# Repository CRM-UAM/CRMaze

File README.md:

# CRMaze
Open source robot for maze solving + line following

Authors
--
**Víctor Uceda & Carlos García**  
Club de Robótica-Mecatrónica, Universidad Autónoma de Madrid (CRM-UAM)  
<http://crm-uam.github.io>  

License
--
License: **Attribution - Share Alike - Creative Commons (<http://creativecommons.org/licenses/by-sa/4.0/>)**  

Disclaimer  
--
This hardware/software is provided "as is", and you use the hardware/software at your own risk. Under no circumstances shall any author be liable for direct, indirect, special, incidental, or consequential damages resulting from the use, misuse, or inability to use this hardware/software, even if the authors have been advised of the possibility of such damages.

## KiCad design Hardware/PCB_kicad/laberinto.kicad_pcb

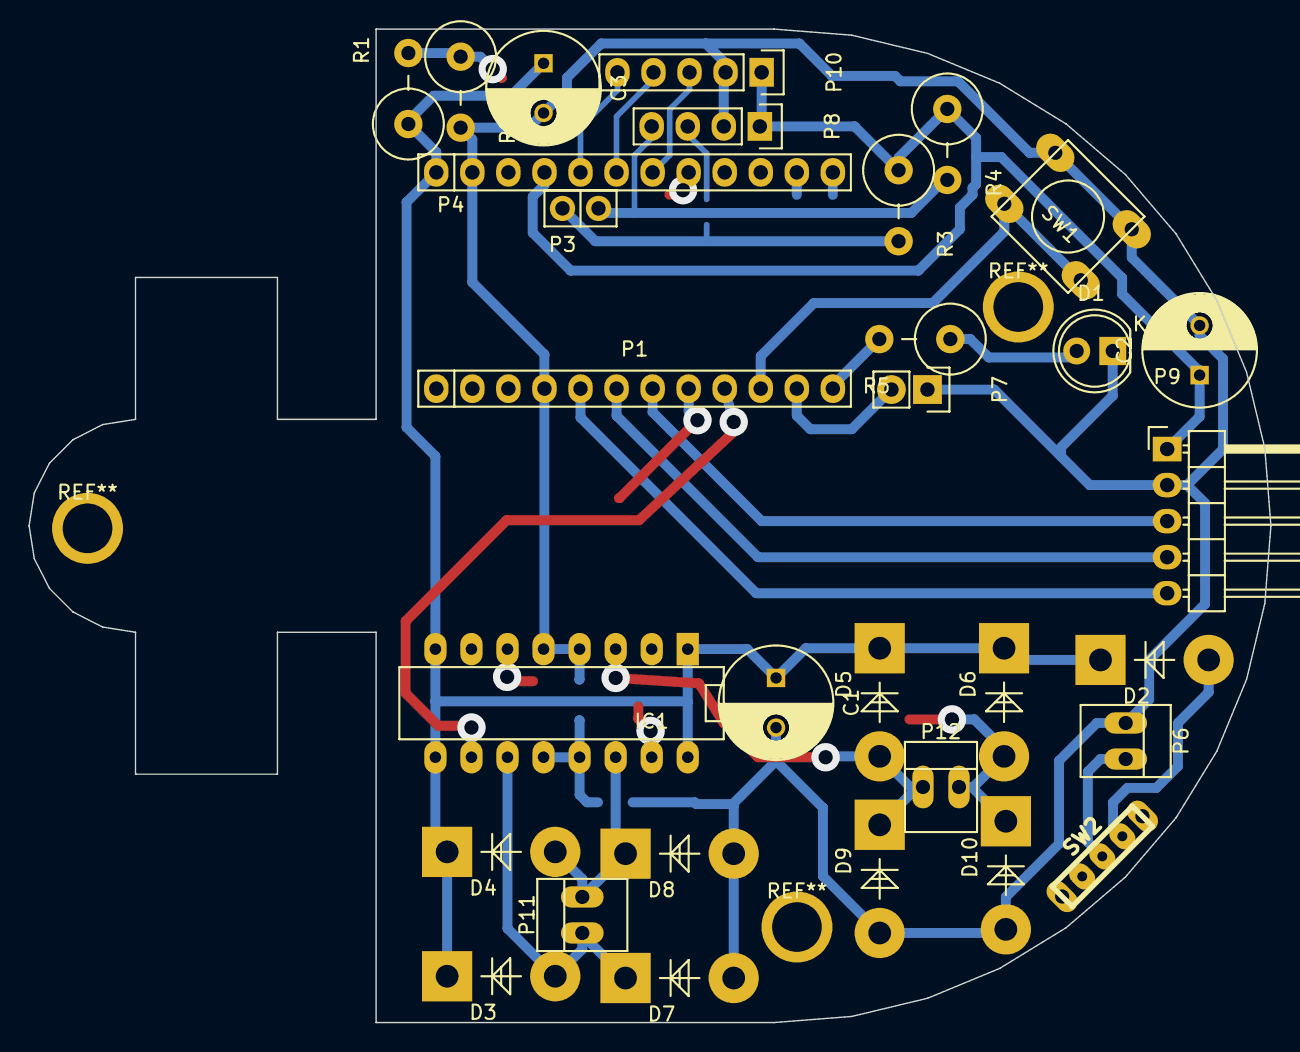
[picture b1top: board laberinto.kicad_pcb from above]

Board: 2 copper layers, 87.5 x 70.0 mm, 31 parts (0 on the bottom side), 27 nets.

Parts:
C1, C2, C3: CP; C_Radial_D8_L11.5_P3.5
D1: CLED; LED-5MM
D2: Dbatt; custom_diode
D3, D4, D5, D6, D7, D8, D9, D10: D; custom_diode
IC1: L293D; DIP-16__300_ELL
P1: Digital; Socket_Strip_Arduino_1x12
P3: ADC; Socket_Strip_Arduino_1x02
P4: Analog; Socket_Strip_Arduino_1x12
P6: batt; PINHEAD1-2
P7: buzzer; Pin_Header_Straight_1x02
P8: I2C_IMU; Pin_Header_Straight_1x04
P9: line_ir; Pin_Header_Angled_1x05
P10: distance; Pin_Header_Straight_1x05
P11: M1; PINHEAD1-2
P12: M2; PINHEAD1-2
R1, R2, R3, R4, R5: R; Resistor_Vertical_RM5mm
SW1: SW_PUSH; SW_PUSH_SMALL
SW2: SWITCH_INV; SWITCH_3Pin

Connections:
+BATT: C1.1, C3.1, D2.2, D3.2, D4.2, D5.2, D6.2, IC1.1, IC1.8, IC1.9, IC1.16, P4.1, R1.1
/Reset: P1.3, P4.3
GND: C1.2, C2.2, C3.2, D1.1, D7.1, D8.1, D9.1, D10.1, IC1.4, IC1.5, IC1.12, IC1.13, P1.4, P4.2, P6.1, P7.1, P8.2, P9.2, P10.2, R2.2, SW1.2
IR1: P4.7, P10.3
IR2: P4.6, P10.4
IR3: P4.5, P10.5
IRL: P1.7, P9.3
IRM: P1.6, P9.4
IRR: P1.5, P9.5
M1A: IC1.2, P4.11
M1Y: D5.1, D9.2, IC1.3, P12.1
M2A: IC1.7, P4.12
M2Y: D6.1, D10.2, IC1.6, P12.2
M3A: IC1.10, P1.9
M3Y: D3.1, D7.2, IC1.11, P11.1
M4A: IC1.15, P1.8
M4Y: D4.1, D8.2, IC1.14, P11.2
unnamed: D1.2, R5.1
unnamed: D2.1, SW2.1
unnamed: P6.2, SW2.2
SCL: P3.1, P8.3, R3.2
SDA: P3.2, P8.4, R4.2
VCC: C2.1, P4.4, P8.1, P9.1, P10.1, R3.1, R4.1
button: P1.10, SW1.1
buzzer: P1.11, P7.2
led: P1.12, R5.2
mbatt: P4.8, R1.2, R2.1

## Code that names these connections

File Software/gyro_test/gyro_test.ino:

// Code for the CRMaze robot
// By Víctor Uceda & Carlos García
//   Club de Robótica-Mecatrónica,
//   Universidad Autónoma de Madrid
//   http://crm-uam.github.io
// License: CC-BY-SA (http://creativecommons.org/licenses/by-sa/4.0/)
//
// Derived from:
//   GNBot ( https://github.com/carlosgs/GNBot )

#define LED_RED_PIN     13
#define LED_GREEN_PIN   9
#define BUZZER_PIN      8
#define LINE_R_PIN      2
#define LINE_M_PIN      3
#define LINE_L_PIN      4
#define M4A_PIN         5
#define M3A_PIN         6
#define BUTTON_PIN      7
#define DIST_3_PIN      A3
#define DIST_2_PIN      A2
#define DIST_1_PIN      A1
#define BATTERY_V_PIN   A0
#define M1A_PIN         11
#define M2A_PIN         10


// IMU
#include "I2Cdev.h"
#include "MPU6050_6Axis_MotionApps20.h"
#if I2CDEV_IMPLEMENTATION == I2CDEV_ARDUINO_WIRE
#include "Wire.h"
#endif

MPU6050 mpu;

// MPU control/status vars
bool dmpReady = false;  // set true if DMP init was successful
uint8_t mpuIntStatus;   // holds actual interrupt status byte from MPU
uint16_t packetSize;    // expected DMP packet size (default is 42 bytes)
uint16_t fifoCount;     // count of all bytes currently in FIFO
uint8_t fifoBuffer[64]; // FIFO storage buffer

// orientation/motion vars
Quaternion q;           // [w, x, y, z]         quaternion container
VectorFloat gravity;    // [x, y, z]            gravity vector
float ypr[3];           // [yaw, pitch, roll]   yaw/pitch/roll container and gravity vector

int setupIMU() {
    // join I2C bus (I2Cdev library doesn't do this automatically)
    #if I2CDEV_IMPLEMENTATION == I2CDEV_ARDUINO_WIRE
      Wire.begin();
      TWBR = 24; // 400kHz I2C clock (200kHz if CPU is 8MHz)
    #elif I2CDEV_IMPLEMENTATION == I2CDEV_BUILTIN_FASTWIRE
      Fastwire::setup(400, true);
    #endif

    mpu.initialize();
/*    mpu.setZGyroOffset(0);*/
/*    */
/*    delay(500);*/
/*    */
/*    int16_t ax, ay, az;*/
/*    int16_t gx, gy, gz;*/
/*    int gzf = 0; // Filtered Z gyro measurement*/
/*    for(int i=0; i<16; i++) {*/
/*        mpu.getMotion6(&ax, &ay, &az, &gx, &gy, &gz);*/
/*        gzf += (int)gz;*/
/*        delay(100);*/
/*    }*/
/*    gzf = round(((float)gzf)/16.);*/

    uint8_t devStatus = mpu.dmpInitialize(); //(0 = success, !0 = error)

    if (devStatus == 0) {
        // Apply the newly-calibrated offset
        //mpu.setZGyroOffset(-gzf);

        mpu.setDMPEnabled(true);
        mpuIntStatus = mpu.getIntStatus();
        // Get the expected DMP packet size for later comparison
        packetSize = mpu.dmpGetFIFOPacketSize();
        dmpReady = true;
    }
    return devStatus;
}

void readIMU_YawPitchRoll(float *data) {
    mpu.resetFIFO();

    // Wait for correct available data length
    fifoCount = mpu.getFIFOCount();
    while (fifoCount < packetSize) fifoCount = mpu.getFIFOCount();

    // Read a packet from FIFO
    mpu.getFIFOBytes(fifoBuffer, packetSize);

    mpu.dmpGetQuaternion(&q, fifoBuffer);
    mpu.dmpGetGravity(&gravity, &q);
    mpu.dmpGetYawPitchRoll(ypr, &q, &gravity);
}


// --- BUTTON ---

//void init_button_pin() {
//    pinMode(BUTTON_PIN,INPUT);
//    digitalWrite(BUTTON_PIN, HIGH); // Enable internal pull-up resistor
//}
//
//// Returns 1 if the button is being pressed, 0 if it is not
//int button_is_pressed() {
//    return !digitalRead(BUTTON_PIN);
//}






//float getDistanceCM(int pin) {
//    float measurement = analogRead(pin);
//    float ir_K = 4419.36; // Linearization of the sensor response
//    float ir_C = 32.736;
//    if(measurement <= ir_C) return 150;
//    float res = ir_K/(measurement-ir_C);
//    if(res < 0 || res > 150) res = 150;
//    return res;
//}



//float mapf(float x, float in_min, float in_max, float out_min, float out_max)
//{
//    return (x - in_min) * (out_max - out_min) / (in_max - in_min) + out_min;
//}
//
//float getBatteryVoltage() {
//    int val = analogRead(BATTERY_V_PIN);
//    return mapf(val,0,1023, 0,21.1765); // Voltage divider with 22k in series with 6k8
//}


void setup() {
    delay(1000);
    
    int ret = setupIMU();
    
    Serial.begin(115200);
    
    //init_button_pin();
    
    // To-Do: decide on a cut-off/warning voltage value
    // Low battery notification (program will stop here if 16.5V are not available)
    //if(getBatteryVoltage() < 16.5)
    //  unrecoverable_error("Battery voltage is too low");
    
    if(ret == 0) {
      //Serial.println("IMU calibration...");
      delay(20000);
      //Serial.println("IMU successfully initialized :-)");
    }// else Serial.println("Error while initializing IMU :-(");
}

void loop() {
    readIMU_YawPitchRoll(ypr);
    Serial.println(ypr[0]);
    delay(100);
}

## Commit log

2015-10-28 Generated schematic & layout
2015-10-28 Linked authors
2015-10-28 Linked board picture
2015-10-28 Added empty software folder
2015-10-28 Generated wheel stl
2015-10-28 added Software (unfinished version)
2015-10-28 added Readme
2015-10-28 modifed Readme
2015-10-29 Fixed track
2015-10-29 reduced memory cost with Coord object, added readMaze.awk convert tool for maze.txt
2015-10-30 Added IMU code
2015-10-30 Added super optimized code by Davide Gironi
2015-10-30 Added motor+buzzer test
2015-10-30 Updated wheels & code
2015-10-30 antes de liarla parda
2015-10-30 Motor functions
2015-10-30 laberinto correcto
2015-10-31 Added compass & IMU tests. Evaluated memory requirements. Simple angle integration achieved
2015-10-31 The gyro is workinggit add -Agit add -A! :-)
2015-10-31 Implemented yaw proportional controller
2015-10-31 added official Oshwdem mazes
2015-10-31 removed old maze files
2015-10-31 evitar fallo reflood
2015-11-01 Acceleration integrated into displacement
2015-11-02 Formatting and DLPF settings updated
2015-11-03 Updated filter settings
2015-11-03 Updated wheel to minimize the effect of distortions introduced by the 3D printer
2015-11-04 Added PID code
2015-11-04 Added sensor support
2015-11-04 added walls functions
2015-11-04 Prueba de los sensores IR
2015-11-04 sensor_support v2
2015-11-04 Incorporated IR sensor measurements so the robot goes straight
2015-11-04 added walls tester code
2015-11-05 prueba en Lab1
2015-11-05 Ajustes varios
2015-11-05 added return to the origin and createSpeedPath
2015-11-05 added run path
2015-11-06 Calibrado con el tablero oficial
2015-11-11 Removed .DS_Store files
2015-11-11 Added gitignore
2016-02-07 Añadido código que no se había subido a github
2016-02-07 Añadidas algunas fotos del proceso de diseño y construccion del robot
2016-02-07 Añadido backup del vídeo de fresado del PCB
2016-02-18 cuadrado con integracion de gyro
2016-09-08 Añadido laberinto
2016-09-11 columnas laberinto
2016-09-18 Testing...
2016-09-19 More tests
2016-09-26 Nuevo diseño de laberinto con columnas y paredes por separado y montaje por inserciones
2016-10-20 Añadida foto
2017-10-31 Añadidas piezas laberinto 2017
2017-10-31 Añadida nota sobre las paredes
